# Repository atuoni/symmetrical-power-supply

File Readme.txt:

- This is a symmetrical power supply whose output can be adjusted up to +15V and -15V, thus 
this power supply should be used with a adjustable power supply up to 30V at its input.
- The maximum output current is 5A.
- If the input voltage is greater than 30V, the fuse will blow for protection.

- I added the gerbers files of PCB. The files were made in Kicad software.
- The .pdf files are the schematic and pcb layout.

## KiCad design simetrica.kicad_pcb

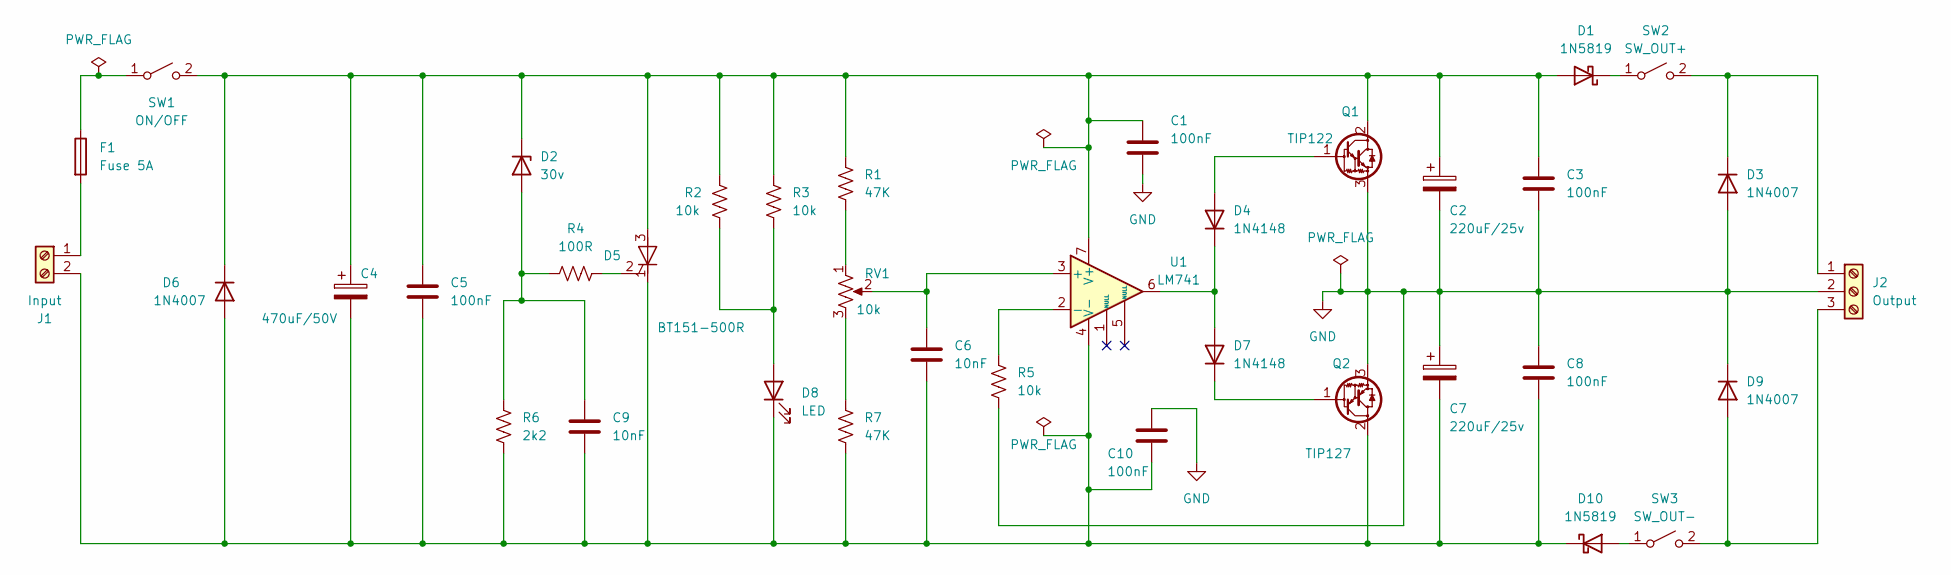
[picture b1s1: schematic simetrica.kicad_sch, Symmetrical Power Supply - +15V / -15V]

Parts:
C1, C3, C5, C8, C10: 100nF; C_Disc_D5.0mm_W2.5mm_P5.00mm
C2, C7: 220uF/25v; CP_Radial_D8.0mm_P3.50mm
C4: 470uF/50V; CP_Radial_D13.0mm_P5.00mm
C6, C9: 10nF; C_Disc_D5.0mm_W2.5mm_P5.00mm
D1, D10: 1N5819; D_DO-41_SOD81_P10.16mm_Horizontal
D2: 30v; D_DO-35_SOD27_P7.62mm_Horizontal
D3, D6, D9: 1N4007; D_DO-41_SOD81_P10.16mm_Horizontal
D4, D7: 1N4148; D_DO-41_SOD81_P10.16mm_Horizontal
D5: BT151-500R; TO-220-3_Vertical
D8: LED; LED_D3.0mm
F1: Fuse 5A; TestPoint_2Pads_Pitch5.08mm_Drill1.3mm
J1: Input; TerminalBlock_Phoenix_MKDS-1,5-2-5.08_1x02_P5.08mm_Horizont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
J2: Output; TerminalBlock_Phoenix_MKDS-1,5-3-5.08_1x03_P5.08mm_Horizont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
Q1: TIP122; TO-220-3_Vertical
Q2: TIP127; TO-220-3_Vertical
R1, R7: 47K; R_Axial_DIN0207_L6.3mm_D2.5mm_P10.16mm_Horizontal
R2, R3, R5: 10k; R_Axial_DIN0207_L6.3mm_D2.5mm_P10.16mm_Horizontal
R4: 100R; R_Axial_DIN0207_L6.3mm_D2.5mm_P10.16mm_Horizontal
R6: 2k2; R_Axial_DIN0207_L6.3mm_D2.5mm_P10.16mm_Horizontal
RV1: 10k; Potentiometer_Bourns_3296W_Vertical
SW1: ON/OFF; TestPoint_2Pads_Pitch5.08mm_Drill1.3mm
SW2: SW_OUT+; TestPoint_2Pads_Pitch5.08mm_Drill1.3mm
SW3: SW_OUT-; TestPoint_2Pads_Pitch5.08mm_Drill1.3mm
U1: LM741; DIP-8_W7.62mm

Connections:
GND: C1.2, C2.2, C3.2, C7.1, C8.1, C10.1, D3.2 (A), D9.1 (K), J2.2, Q1.3 (E), Q2.3 (E), R5.2
unnamed: C1.1, C2.1, C3.1, C4.1, C5.1, D1.2 (A), D2.1 (K), D5.3 (A), D6.1 (K), Q1.2 (C), R1.1, R2.1, R3.1, SW1.2 (B), U1.7 (V+)
unnamed: D1.1 (K), SW2.1 (A)
unnamed: C9.1, D2.2 (A), R4.1, R6.1
unnamed: D3.1 (K), J2.1, SW2.2 (B)
unnamed: D4.2 (A), Q1.1 (B)
unnamed: D4.1 (K), D7.2 (A), U1.6
unnamed: D5.2 (G), R4.2
unnamed: D7.1 (K), Q2.1 (B)
unnamed: D8.2 (A), R2.2, R3.2
unnamed: D9.2 (A), J2.3, SW3.2 (B)
unnamed: D10.2 (A), SW3.1 (A)
unnamed: C4.2, C5.2, C6.2, C7.2, C8.2, C9.2, C10.2, D5.1 (K), D6.2 (A), D8.1 (K), D10.1 (K), J1.2, Q2.2 (C), R6.2, R7.2, U1.4 (V-)
unnamed: F1.2, J1.1
unnamed: R1.2, RV1.1
unnamed: R7.1, RV1.3
unnamed: F1.1, SW1.1 (A)
unnamed: C6.1, RV1.2, U1.3 (+)
unnamed: R5.1, U1.2 (-)

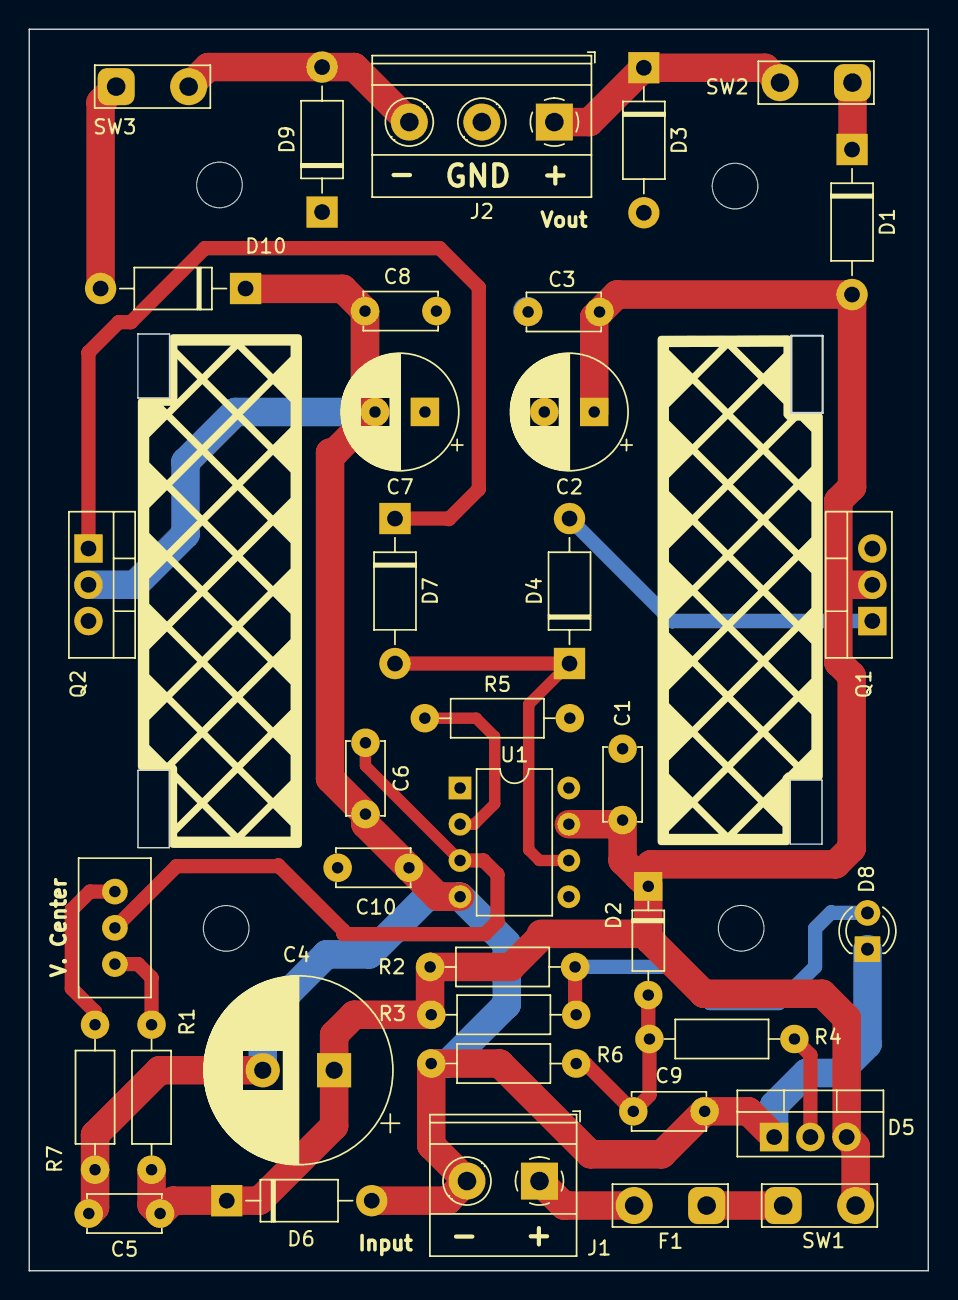
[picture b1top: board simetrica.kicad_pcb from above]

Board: 2 copper layers, 63.0 x 87.0 mm, 37 parts (0 on the bottom side), 19 nets.

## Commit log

2024-02-04 version 2.0
